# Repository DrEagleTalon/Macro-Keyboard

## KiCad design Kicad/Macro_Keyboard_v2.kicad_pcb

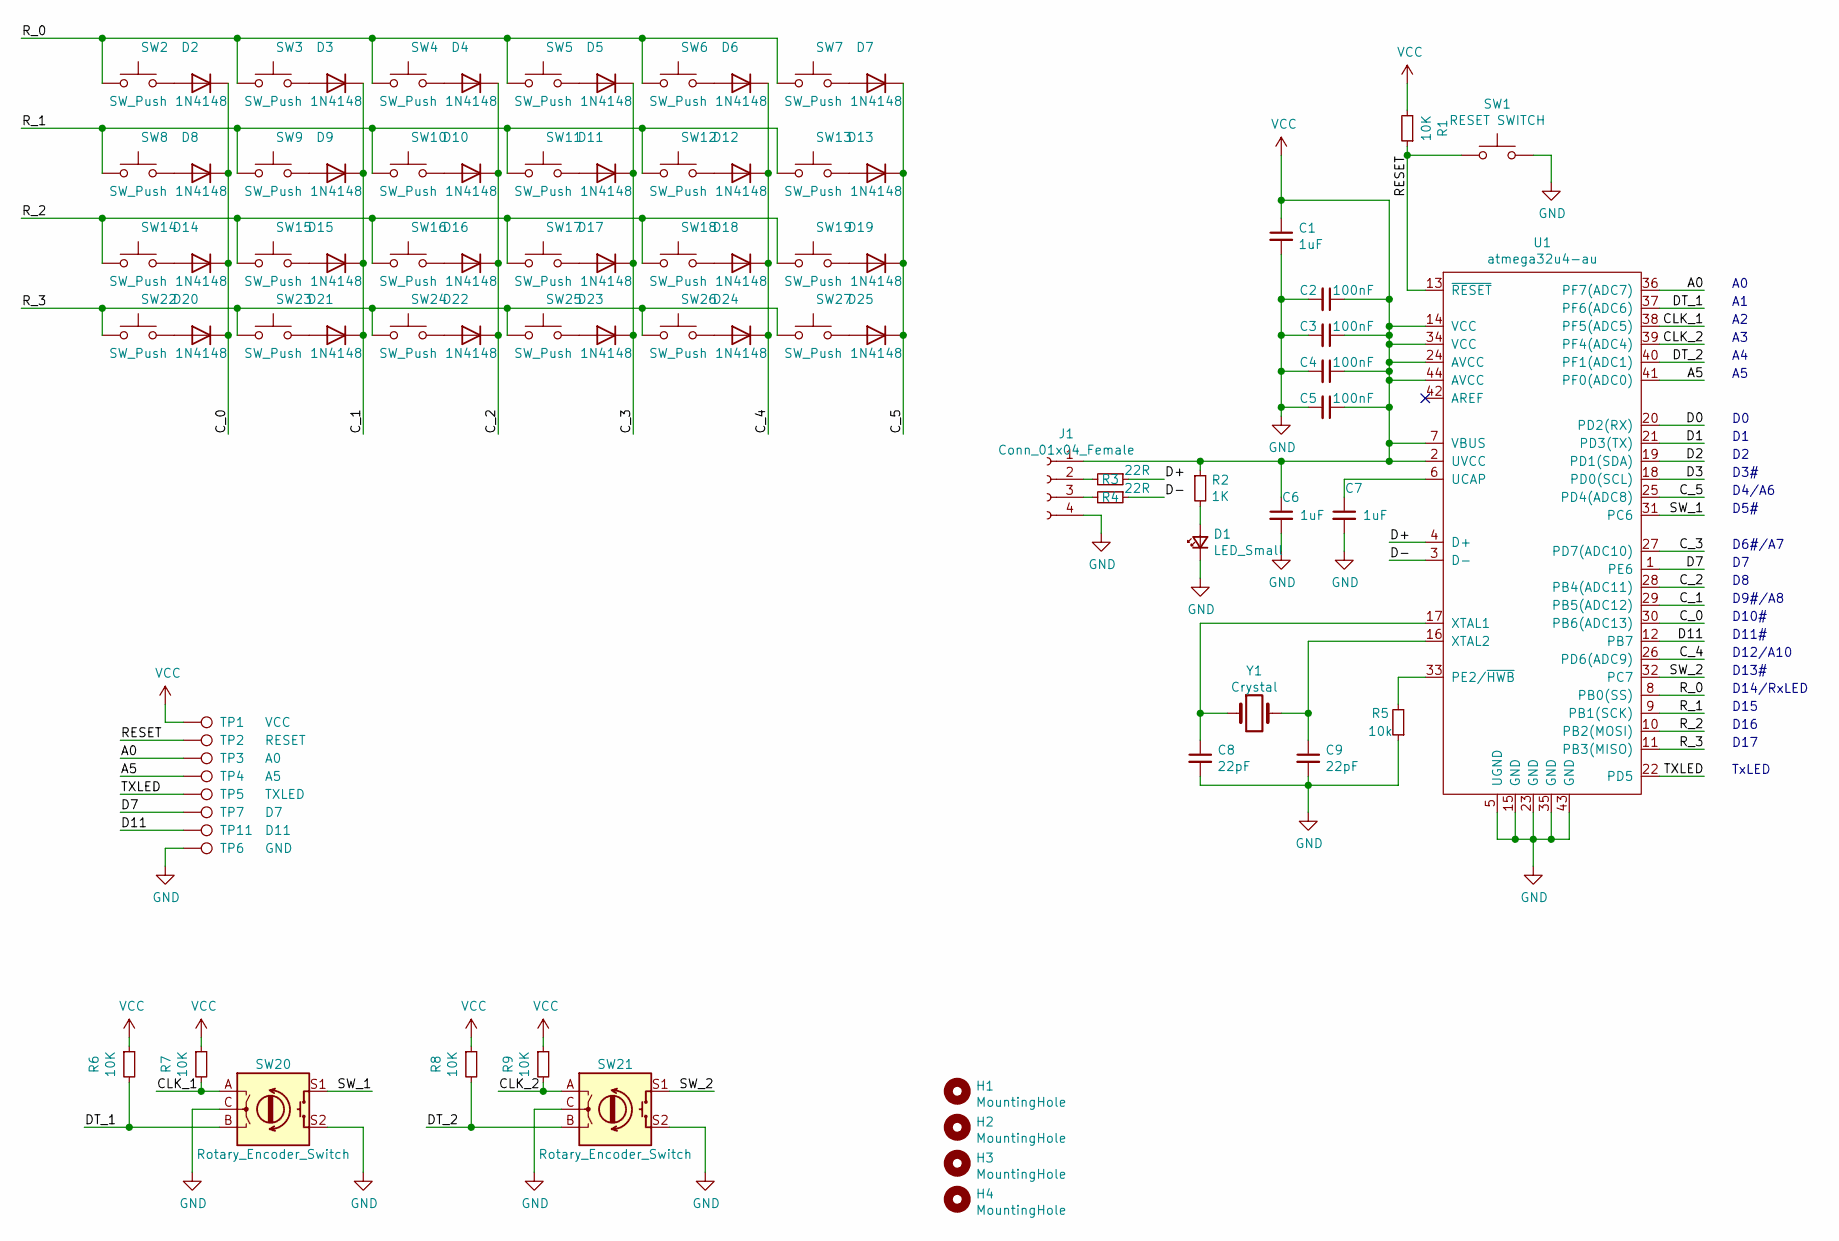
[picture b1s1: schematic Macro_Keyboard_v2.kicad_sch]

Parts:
C1, C6, C7: 1uF; C_0603_1608Metric_Pad1.08x0.95mm_HandSolder; LCSC C15849
C2, C3, C4, C5: 100nF; C_0603_1608Metric_Pad1.08x0.95mm_HandSolder; LCSC C83054
C8, C9: 22pF; C_0603_1608Metric_Pad1.08x0.95mm_HandSolder; LCSC C1653
D1: LED_Small; LED_0603_1608Metric_Pad1.05x0.95mm_HandSolder; LCSC C72044
D2, D3, D4, D5, D6, D7, D8, D9, D10, D11, D12, D13, D14, D15, D16, D17, D18, D19, D20, D21, D22, D23, D24, D25: 1N4148; D_SOD-123; LCSC C81598
H1, H2, H3, H4: MountingHole; MountingHole_3.2mm_M3_DIN965_Pad
J1: Conn_01x04_Female; JST_XH_B4B-XH-A_1x04_P2.50mm_Vertical
R1, R6, R7, R8, R9: 10K; R_0603_1608Metric_Pad0.98x0.95mm_HandSolder; LCSC C25804
R2: 1K; R_0603_1608Metric_Pad0.98x0.95mm_HandSolder; LCSC C4177
R3, R4: 22R; R_0603_1608Metric_Pad0.98x0.95mm_HandSolder; LCSC C23345
R5: 10k; R_0603_1608Metric_Pad0.98x0.95mm_HandSolder; LCSC C25804
SW1: RESET SWITCH; SW_SPST_SKQG_WithStem; LCSC C92584
SW2, SW3, SW4, SW5, SW6, SW7, SW8, SW9, SW10, SW11, SW12, SW13, SW14, SW15, SW16, SW17, SW18, SW19, SW22, SW23, SW24, SW25, SW26, SW27: SW_Push; SW_Cherry_MX_1.00u_PCB
SW20, SW21: Rotary_Encoder_Switch; RotaryEncoder_Alps_EC11E-Switch_Vertical_H20mm
TP1: VCC; PinHeader_1x01_P2.54mm_Vertical
TP2: RESET; TestPoint_Keystone_5015_Micro-Minature
TP3: A0; TestPoint_Keystone_5015_Micro-Minature
TP4: A5; PinHeader_1x01_P2.54mm_Vertical
TP5: TXLED; TestPoint_Keystone_5015_Micro-Minature
TP6: GND; PinHeader_1x01_P2.54mm_Vertical
TP7: D7; TestPoint_Keystone_5015_Micro-Minature
TP11: D11; TestPoint_Keystone_5015_Micro-Minature
U1: atmega32u4-au; TQFP-44_10x10mm_P0.8mm; LCSC C44854
Y1: Crystal; Crystal_SMD_3225-4Pin_3.2x2.5mm

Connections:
/A0: TP3.1, U1.36 (PF7(ADC7))
/A5: TP4.1, U1.41 (PF0(ADC0))
/CLK_1: R7.2, SW20.A, U1.38 (PF5(ADC5))
/CLK_2: R9.2, SW21.A, U1.39 (PF4(ADC4))
/C_0: D2.1 (K), D8.1 (K), D14.1 (K), D20.1 (K), U1.30 (PB6(ADC13))
/C_1: D3.1 (K), D9.1 (K), D15.1 (K), D21.1 (K), U1.29 (PB5(ADC12))
/C_2: D4.1 (K), D10.1 (K), D16.1 (K), D22.1 (K), U1.28 (PB4(ADC11))
/C_3: D5.1 (K), D11.1 (K), D17.1 (K), D23.1 (K), U1.27 (PD7(ADC10))
/C_4: D6.1 (K), D12.1 (K), D18.1 (K), D24.1 (K), U1.26 (PD6(ADC9))
/C_5: D7.1 (K), D13.1 (K), D19.1 (K), D25.1 (K), U1.25 (PD4(ADC8))
/D0: U1.20 (PD2(RX))
/D1: U1.21 (PD3(TX))
/D2: U1.19 (PD1(SDA))
/D3: U1.18 (PD0(SCL))
/D7: TP7.1, U1.1 (PE6)
/D11: TP11.1, U1.12 (PB7)
/D+: R3.1, U1.4 (D+)
/D-: R4.1, U1.3 (D-)
/DT_1: R6.2, SW20.B, U1.37 (PF6(ADC6))
/DT_2: R8.2, SW21.B, U1.40 (PF1(ADC1))
/RESET: R1.1, SW1.1, TP2.1, U1.13 (~RESET)
/R_0: SW2.1, SW3.1, SW4.1, SW5.1, SW6.1, SW7.1, U1.8 (PB0(SS))
/R_1: SW8.1, SW9.1, SW10.1, SW11.1, SW12.1, SW13.1, U1.9 (PB1(SCK))
/R_2: SW14.1, SW15.1, SW16.1, SW17.1, SW18.1, SW19.1, U1.10 (PB2(MOSI))
/R_3: SW22.1, SW23.1, SW24.1, SW25.1, SW26.1, SW27.1, U1.11 (PB3(MISO))
/SW_1: SW20.S1, U1.31 (PC6)
/SW_2: SW21.S1, U1.32 (PC7)
/TXLED: TP5.1, U1.22 (PD5)
GND: C1.2, C2.2, C3.2, C4.2, C5.2, C6.2, C7.2, C8.2, C9.2, D1.1 (K), J1.4, R5.1, SW1.2, SW20.C, SW20.S2, SW21.C, SW21.S2, TP6.1, U1.5 (UGND), U1.15 (GND), U1.23 (GND), U1.35 (GND), U1.43 (GND)
unnamed: C7.1, U1.6 (UCAP)
unnamed: C8.1, U1.17 (XTAL1), Y1.1
unnamed: C9.1, U1.16 (XTAL2), Y1.2
unnamed: D1.2 (A), R2.2
unnamed: D2.2 (A), SW2.2
unnamed: D3.2 (A), SW3.2
unnamed: D4.2 (A), SW4.2
unnamed: D5.2 (A), SW5.2
unnamed: D6.2 (A), SW6.2
unnamed: D7.2 (A), SW7.2
unnamed: D8.2 (A), SW8.2
unnamed: D9.2 (A), SW9.2
unnamed: D10.2 (A), SW10.2
unnamed: D11.2 (A), SW11.2
unnamed: D12.2 (A), SW12.2
unnamed: D13.2 (A), SW13.2
unnamed: D14.2 (A), SW14.2
unnamed: D15.2 (A), SW15.2
unnamed: D16.2 (A), SW16.2
unnamed: D17.2 (A), SW17.2
unnamed: D18.2 (A), SW18.2
unnamed: D19.2 (A), SW19.2
unnamed: D20.2 (A), SW22.2
unnamed: D21.2 (A), SW23.2
unnamed: D22.2 (A), SW24.2
unnamed: D23.2 (A), SW25.2
unnamed: D24.2 (A), SW26.2
unnamed: D25.2 (A), SW27.2
unnamed: J1.2, R3.2
unnamed: J1.3, R4.2
unnamed: R5.2, U1.33 (PE2/~HWB)
VCC: C1.1, C2.1, C3.1, C4.1, C5.1, C6.1, J1.1, R1.2, R2.1, R6.1, R7.1, R8.1, R9.1, TP1.1, U1.2 (UVCC), U1.7 (VBUS), U1.14 (VCC), U1.24 (AVCC), U1.34 (VCC), U1.44 (AVCC)

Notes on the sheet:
D3#
D4/A6
D5#
D6#/A7
D9#/A8
D10#
D11#
D12/A10
D13#
D14/RxLED
D15
D16
D17
TxLED

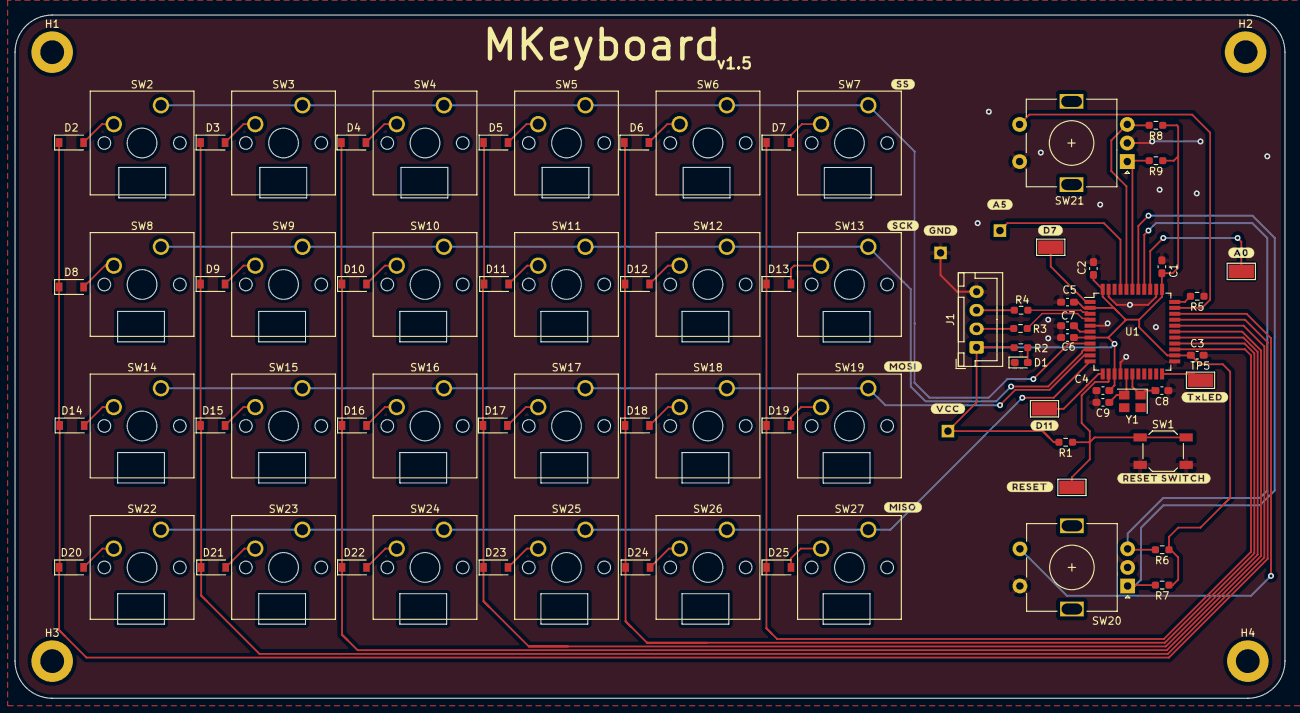
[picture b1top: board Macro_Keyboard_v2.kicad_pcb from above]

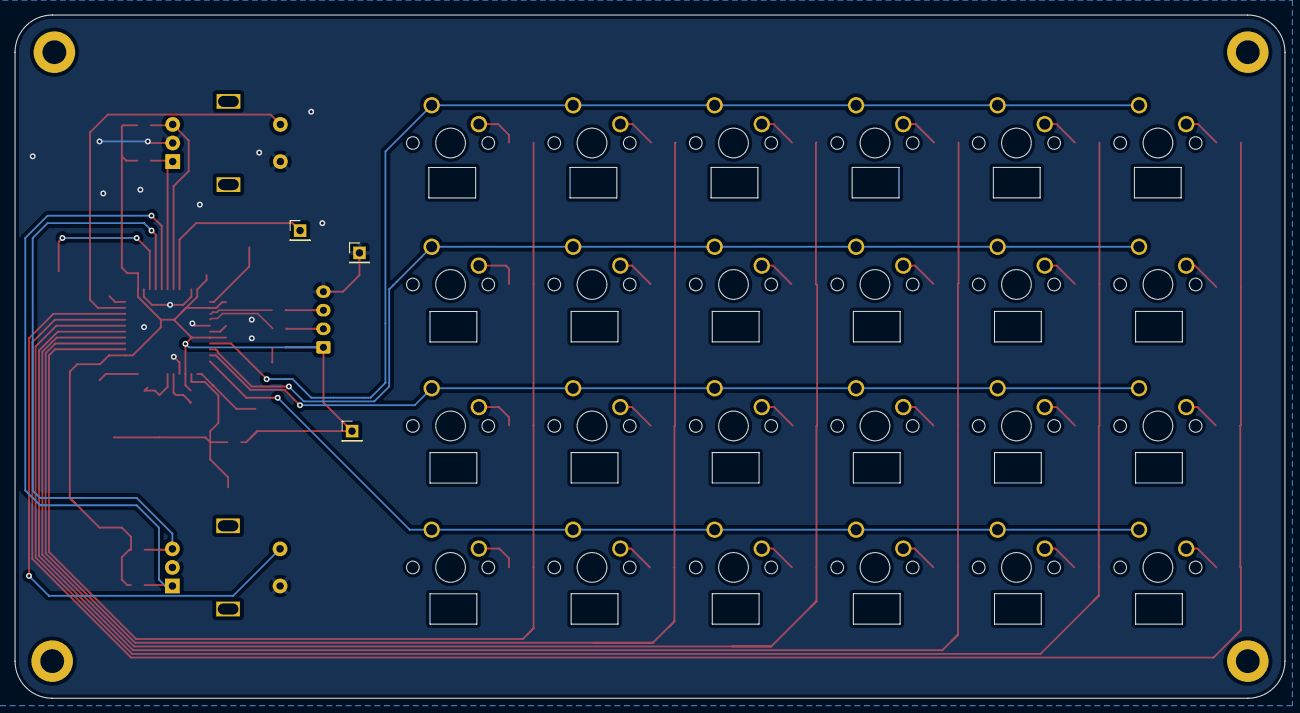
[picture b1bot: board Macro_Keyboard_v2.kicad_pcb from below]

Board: 2 copper layers, 171.0 x 92.0 mm, 85 parts (3 on the bottom side), 57 nets.

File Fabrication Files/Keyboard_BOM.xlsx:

Comment | Designator | Footprint | LCSC
1uF | C1,C6,C7 | Capacitor_SMD:C_0603_1608Metric_Pad1.08x0.95mm_HandSolder | C15849
100nF | C2,C3,C4,C5 | Capacitor_SMD:C_0603_1608Metric_Pad1.08x0.95mm_HandSolder | C268011
22pF | C8,C9 | Capacitor_SMD:C_0603_1608Metric_Pad1.08x0.95mm_HandSolder | C1653
LED_Small | D1 | LED_SMD:LED_0603_1608Metric_Pad1.05x0.95mm_HandSolder | C72044
1N4148 | D2,D3,D4,D5,D6,D7,D8,D9,D10,D11,D12,D13,D14,D15,D16,D17,D18,D19,D20,D21,D22,D23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 | Diode_SMD:D_SOD-123 | C81598
MountingHole | H1,H2,H3,H4 | MountingHole:MountingHole_3.2mm_M3_DIN965_Pad
Conn_01x04_Female | J1 | Connector_JST:JST_XH_B4B-XH-A_1x04_P2.50mm_Vertical
10K | R1,R6,R7,R8,R9 | Resistor_SMD:R_0603_1608Metric_Pad0.98x0.95mm_HandSolder | C25804
1K | R2 | Resistor_SMD:R_0603_1608Metric_Pad0.98x0.95mm_HandSolder | C4177
22R | R3,R4 | Resistor_SMD:R_0603_1608Metric_Pad0.98x0.95mm_HandSolder | C23345
10k | R5 | Resistor_SMD:R_0603_1608Metric_Pad0.98x0.95mm_HandSolder | C25804
RESET SWITCH | SW1 | Button_Switch_SMD:SW_SPST_SKQG_WithStem | C202424
SW_Push | SW2,SW3,SW4,SW5,SW6,SW7,SW8,SW9,SW10,SW11,SW12,SW13,SW14,SW15,SW16,SW17,SW18,SW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 | Button_Switch_Keyboard:SW_Cherry_MX_1.00u_PCB
Rotary_Encoder_Switch | SW20,SW21 | Rotary_Encoder:RotaryEncoder_Alps_EC11E-Switch_Vertical_H20mm
VCC | TP1 | Connector_PinHeader_2.54mm:PinHeader_1x01_P2.54mm_Vertical
D11 | TP11 | TestPoint:TestPoint_Keystone_5015_Micro-Minature
RESET | TP2 | TestPoint:TestPoint_Keystone_5015_Micro-Minature
A0 | TP3 | TestPoint:TestPoint_Keystone_5015_Micro-Minature
A5 | TP4 | Connector_PinHeader_2.54mm:PinHeader_1x01_P2.54mm_Vertical
TXLED | TP5 | TestPoint:TestPoint_Keystone_5015_Micro-Minature
GND | TP6 | Connector_PinHeader_2.54mm:PinHeader_1x01_P2.54mm_Vertical
D7 | TP7 | TestPoint:TestPoint_Keystone_5015_Micro-Minature
atmega32u4-au | U1 | Package_QFP:TQFP-44_10x10mm_P0.8mm | C44854
16MHz | Y1 | Crystal:Crystal_SMD_3225-4Pin_3.2x2.5mm | C15171

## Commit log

2021-04-26 Clean Repo
2021-05-15 little silkscreen update
